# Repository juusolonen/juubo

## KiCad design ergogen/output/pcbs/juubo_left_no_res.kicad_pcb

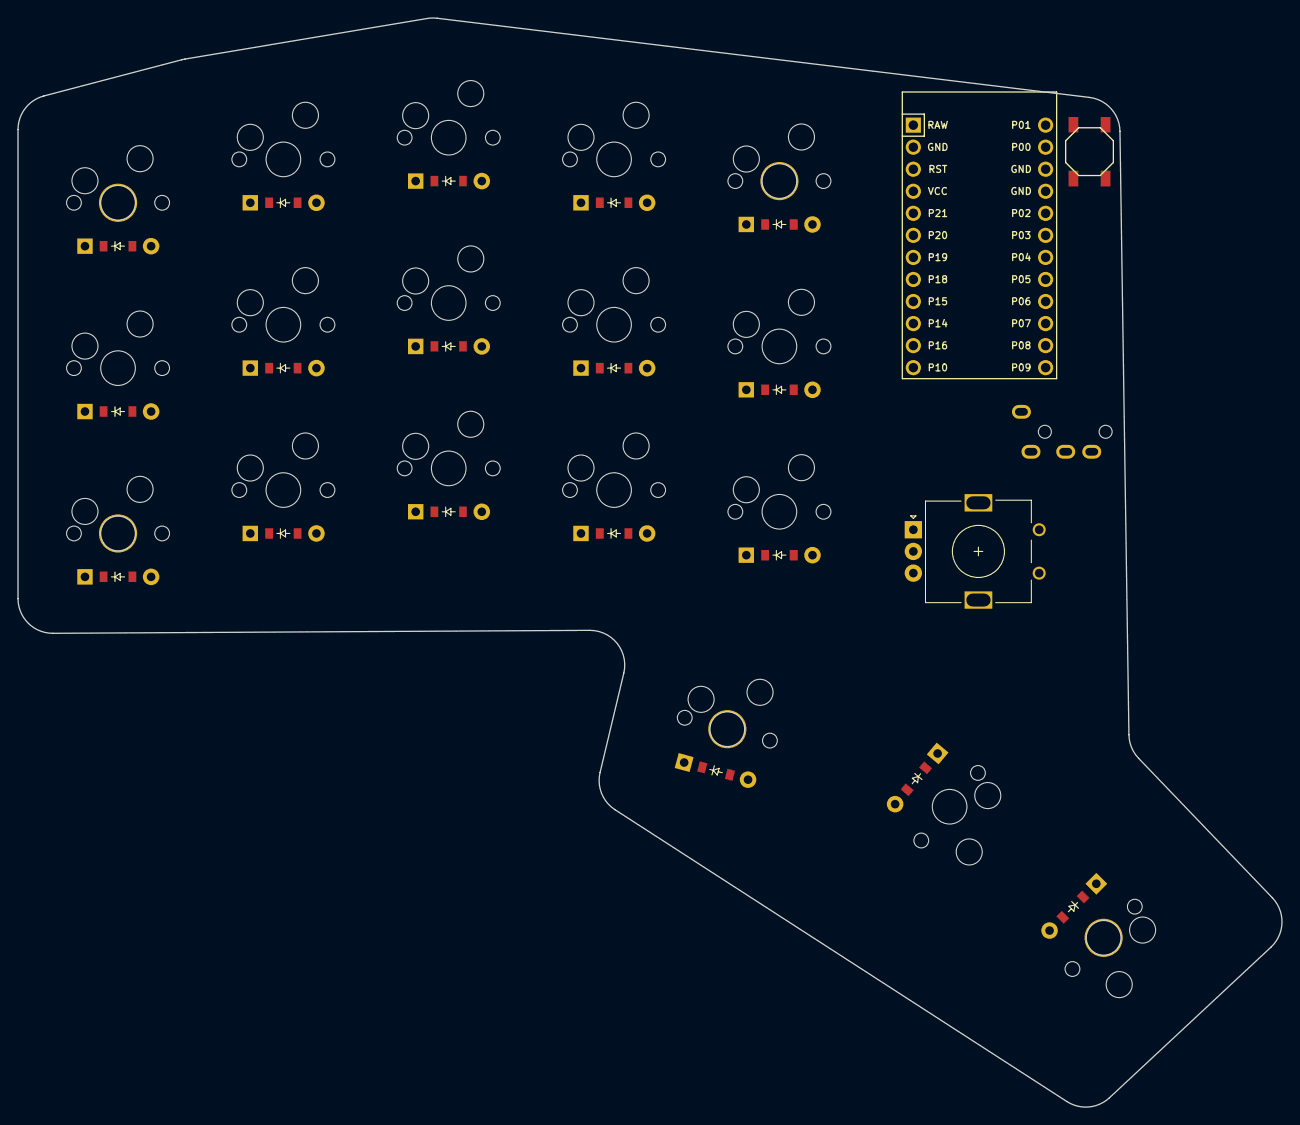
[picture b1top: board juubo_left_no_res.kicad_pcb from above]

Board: 2 copper layers, 145.6 x 125.5 mm, 45 parts (0 on the bottom side), 35 nets, no tracks yet.

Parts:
B1: SW_TACT_ALPS_SKQGABE010
D1, D2, D3, D4, D5, D6, D7, D8, D9, D10, D11, D12, D13, D14, D15, D16, D17, D18: ComboDiode
MCU1: ProMicro
ROT1: rotary_encoder
S1, S2, S3, S4, S5, S6, S7, S8, S9, S10, S11, S12, S13, S14, S15, S16, S17, S18: MX
TRRS1: TRRS-PJ-320A-dual
_1, _2, _3, _4, _5: MountingHole_2.2mm_M2_Pad_Via

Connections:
GND: B1.1, MCU1.2, MCU1.15, MCU1.16, ROT1.2, ROT1.C, TRRS1.4
P1: MCU1.13, S13.1, S14.1, S15.1, S18.1
P2: MCU1.17, TRRS1.2
P3: MCU1.18, TRRS1.3
P7: MCU1.22, ROT1.A
P8: MCU1.23, ROT1.B
P9: MCU1.24, ROT1.1
P10: D16.1, D17.1, D18.1, MCU1.12
P14: D2.1, D5.1, D8.1, D11.1, D14.1, MCU1.10
P15: D3.1, D6.1, D9.1, D12.1, D15.1, MCU1.9
P16: D1.1, D4.1, D7.1, D10.1, D13.1, MCU1.11
P18: MCU1.8, S1.1, S2.1, S3.1
P19: MCU1.7, S4.1, S5.1, S6.1
P20: MCU1.6, S7.1, S8.1, S9.1, S16.1
P21: MCU1.5, S10.1, S11.1, S12.1, S17.1
RST: B1.2, MCU1.3
VCC: MCU1.4, TRRS1.1
extra_cluster: D18.2, S18.2
index_bottom: D10.2, S10.2
index_home: D11.2, S11.2
index_top: D12.2, S12.2
inner_bottom: D13.2, S13.2
inner_home: D14.2, S14.2
inner_top: D15.2, S15.2
layer_cluster: D16.2, S16.2
middle_bottom: D7.2, S7.2
middle_home: D8.2, S8.2
middle_top: D9.2, S9.2
pinky_bottom: D1.2, S1.2
pinky_home: D2.2, S2.2
pinky_top: D3.2, S3.2
ring_bottom: D4.2, S4.2
ring_home: D5.2, S5.2
ring_top: D6.2, S6.2
space_cluster: D17.2, S17.2
